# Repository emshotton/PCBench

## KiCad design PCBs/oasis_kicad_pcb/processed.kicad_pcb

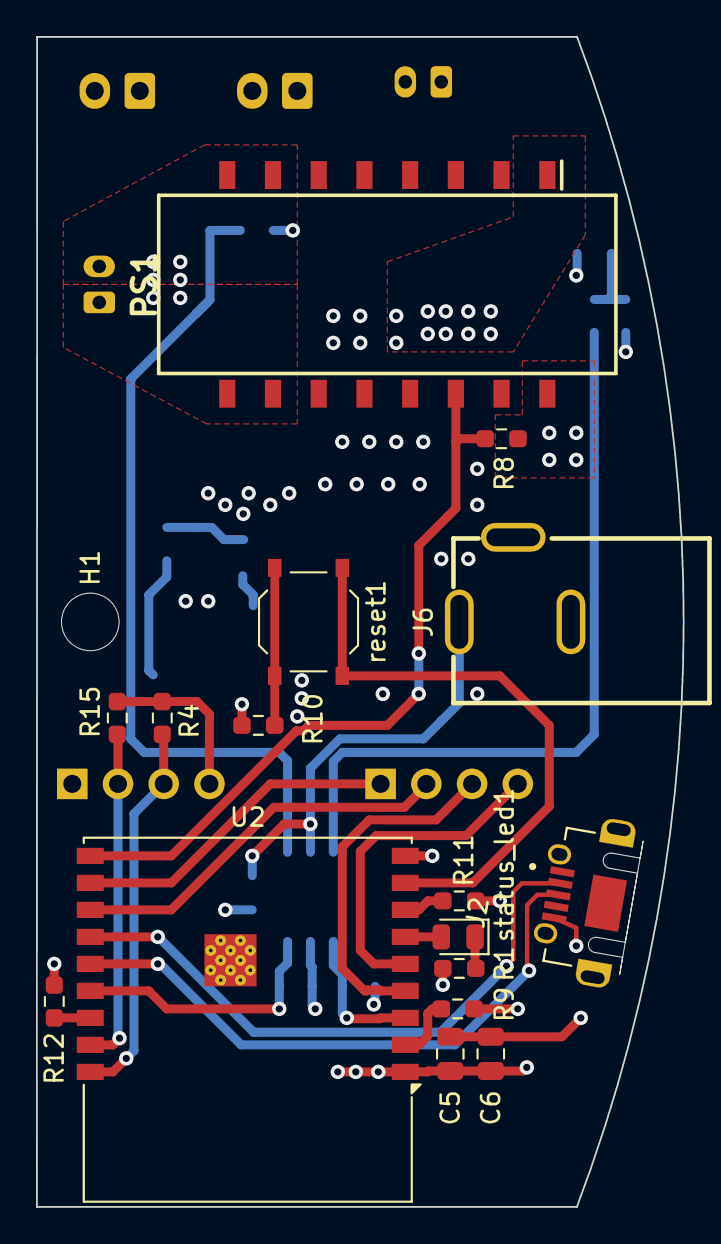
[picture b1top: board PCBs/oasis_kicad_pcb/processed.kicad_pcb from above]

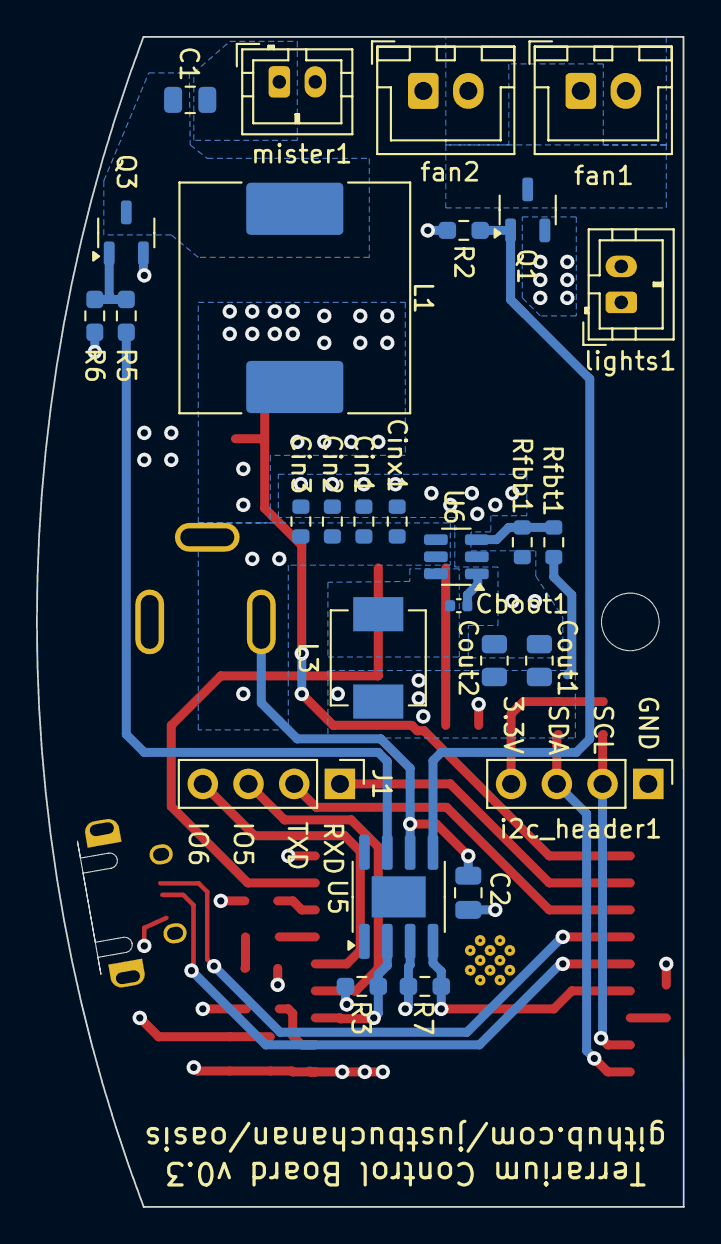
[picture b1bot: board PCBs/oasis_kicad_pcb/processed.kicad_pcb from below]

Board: 4 copper layers, 35.9 x 65.0 mm, 45 parts (28 on the bottom side), 32 nets.

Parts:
C1, C2, C6: .1uF; C_0805_2012Metric
C5: 10uF; C_0805_2012Metric
Cboot1: 100nF; C_0402_1005Metric
Cin1, Cin2, Cin3: 1uF; R_0603_1608Metric
Cinx1: 100nF; R_0603_1608Metric
Cout1, Cout2: 10uF; R_0805_2012Metric
H1: MountingHole; MountingHole_3.2mm_M3
J1: Conn_01x04; PinHeader_1x04_P2.54mm_Vertical
J2: USB_B_Micro; MOLEX_47590-0001
J6: Barrel_Jack_MountingPin; DC-IN-TH_XDJK-0051-025_JLC_C7498153
L1: 330uH; L_SXN_SMDRI127
L3: 10uH; L_Vishay_IHLP-2020
PS1: LDD-700LS; LDD-700LS-SOP254P1280X930-16N
Q1, Q3: Q_NMOS_GDS; SOT-23-3-pinswapped-mosfet
R1: 470; R_0603_1608Metric_Pad0.98x0.95mm_HandSolder
R2, R3, R5, R7, R8, R9, R10, R11, R12: 10k; R_0603_1608Metric_Pad0.98x0.95mm_HandSolder
R4, R15: 4.7k; R_0603_1608Metric_Pad0.98x0.95mm_HandSolder
R6: 10; R_0603_1608Metric_Pad0.98x0.95mm_HandSolder
Rfbb1: 22.1k; R_0603_1608Metric
Rfbt1: 69.8k; R_0603_1608Metric
U2: ESP32-C3-WROOM-02
U5: IX4427N; SOIC-8-1EP_3.9x4.9mm_P1.27mm_EP2.29x3mm
U6: LMR54406DBVR; SOT-23-6
fan1, fan2: Conn_01x02; JST_XH_B2B-XH-A_1x02_P2.50mm_Vertical
i2c_header1: Conn_01x04; PinHeader_1x04_P2.54mm_Vertical
lights1: Conn_01x02; JST_PH_B2B-PH-K_1x02_P2.00mm_Vertical
mister1: Conn_01x02; JST_PH_B2B-PH-K_1x02_P2.00mm_Vertical
reset1: SW_Push; SW_Push_1P1T_XKB_TS-1187A
status_led1: LED; LED_0805_2012Metric

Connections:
+3.3V: C5.1, C6.1, Cout1.1, Cout2.1, L3.2, R4.1, R9.1, R11.1, R12.2, R15.1, Rfbt1.1, U2.1 (3V3), i2c_header1.4
+18V: C2.1, Cin1.1, Cin2.1, Cin3.1, Cinx1.1, J6.1, L1.2, PS1.1 (+VIN), U5.6 (VCC), U6.4 (EN), U6.5 (VIN), fan1.1, fan2.1
/RXD: J1.1, U2.11 (IO20/RXD)
/TXD: J1.2, U2.12 (IO21/TXD)
/fan1_ctl: R3.1, U2.3 (IO4), U5.2 (INA)
/i2c_scl: R15.2, U2.17 (IO1), i2c_header1.2
/i2c_sda: R4.2, U2.18 (IO0), i2c_header1.3
/led_N: PS1.9 (-VOUT_1), PS1.10 (-VOUT_2), lights1.1
/led_P: PS1.7 (+VOUT_1), PS1.8 (+VOUT_2), lights1.2
/led_ctl: PS1.14 (PWM_DIM), R8.1, U2.10 (IO10)
/mist_ctl: R7.1, U2.15 (IO3), U5.4 (INB)
/usb_dminus: J2.2 (D-), U2.13 (IO18)
/usb_dplus: J2.3 (D+), U2.14 (IO19)
GND: C2.2, C5.2, C6.2, Cin1.2, Cin2.2, Cin3.2, Cinx1.2, Cout1.2, Cout2.2, J2.5 (GND), J6.2, PS1.16 (-VIN), Q1.3 (S), Q3.3 (S), R1.1, R2.2, R3.2, R5.2, R7.2, R8.2, R10.1, Rfbb1.2, U2.9 (GND), U2.19 (GND), U5.3 (GND), U6.2 (GND), i2c_header1.1, mister1.2
unnamed: J1.3, U2.4 (IO5)
unnamed: J1.4, U2.5 (IO6)
unnamed: Q1.2 (D), fan1.2, fan2.2
unnamed: Q1.1 (G), R2.1, U5.5 (OUTB)
unnamed: C1.1, L1.1, Q3.2 (D)
unnamed: Q3.1 (G), R5.1, R6.2
unnamed: R10.2, reset1.2
unnamed: R9.2, U2.2 (EN)
unnamed: R12.1, U2.16 (IO2)
unnamed: U2.6 (IO7), status_led1.2 (A)
unnamed: R11.2, U2.7 (IO8)
unnamed: U2.8 (IO9), reset1.1
unnamed: R6.1, U5.7 (OUTA)
unnamed: Cboot1.2, U6.1 (CB)
unnamed: Rfbb1.1, Rfbt1.2, U6.3 (FB)
unnamed: Cboot1.1, L3.1, U6.6 (SW)
unnamed: C1.2, mister1.1
unnamed: R1.2, status_led1.1 (K)

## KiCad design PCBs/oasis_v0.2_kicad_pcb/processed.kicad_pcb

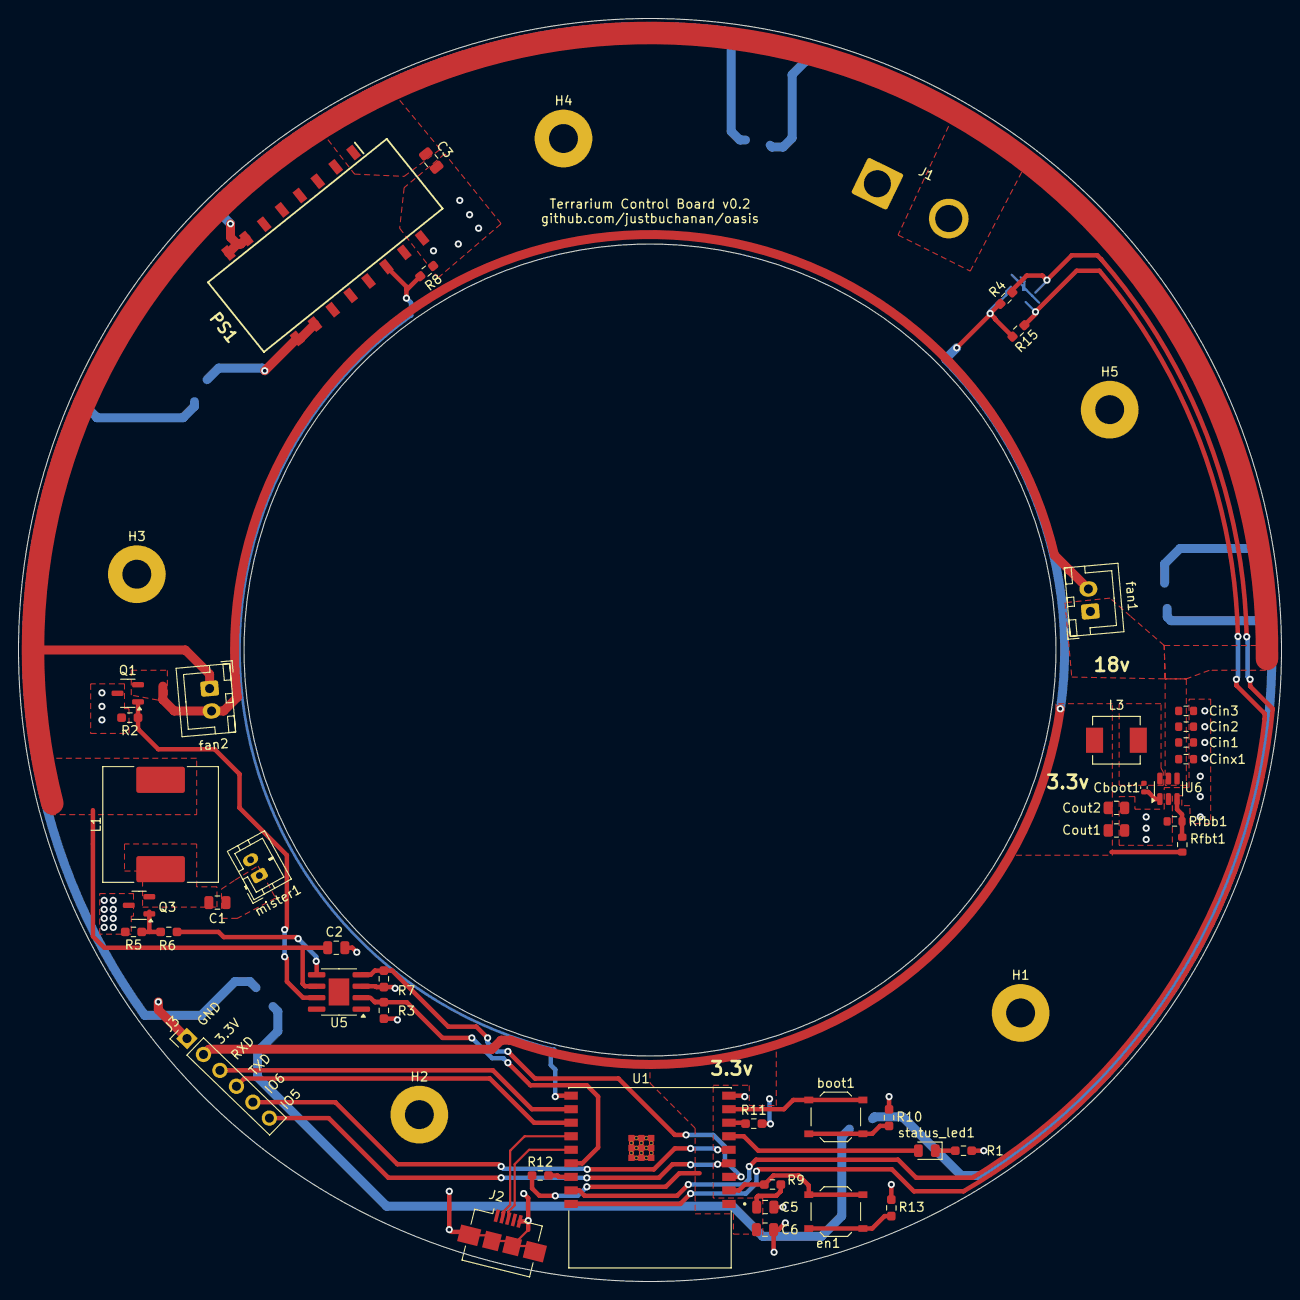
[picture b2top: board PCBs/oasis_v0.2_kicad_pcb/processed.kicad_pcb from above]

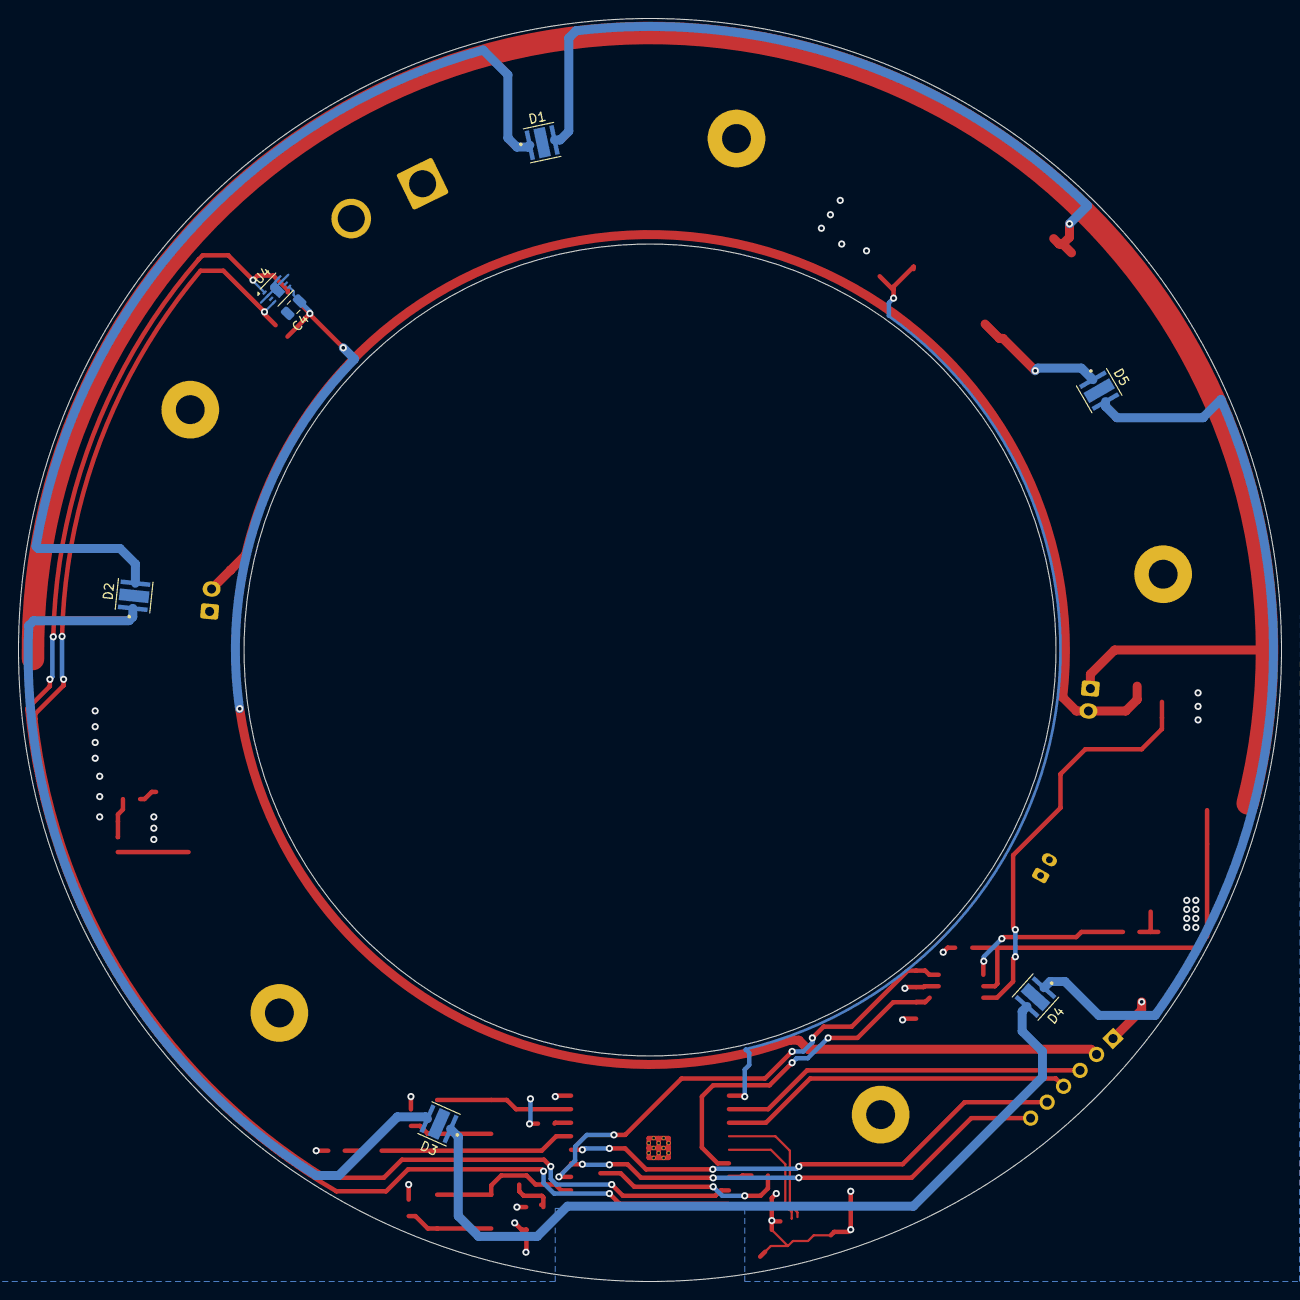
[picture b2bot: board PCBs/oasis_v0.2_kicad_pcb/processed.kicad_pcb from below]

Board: 2 copper layers, 140.0 x 140.0 mm, 57 parts (7 on the bottom side), 37 nets.

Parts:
C1, C2, C3, C4, C6: .1uF; C_0805_2012Metric
C5: 10uF; C_0805_2012Metric
Cboot1: 100nF; C_0402_1005Metric
Cin1, Cin2, Cin3: 1uF; R_0603_1608Metric
Cinx1: 100nF; R_0603_1608Metric
Cout1, Cout2: 10uF; R_0805_2012Metric
D1, D2, D3, D4, D5: LED_Pad; LED_XTEAWT-00-0000-000000F51
H1, H2, H3, H4, H5: MountingHole_Pad; MountingHole_3.2mm_M3_Pad
J1: Conn_01x02; SolderWire-2.5sqmm_1x02_P8.8mm_D2.4mm_OD4.4mm
J2: USB_B_Micro; USB_Micro-B_Amphenol_10104110_Horizontal
J3: Conn_01x06; PinHeader_1x06_P2.54mm_Vertical
L1: 330uH; L_SXN_SMDRI127
L3: 10uH; L_Vishay_IHLP-2020
PS1: LDD-700LS; LDD-700LS-SOP254P1280X930-16N
Q1, Q3: Q_NMOS_GDS; SOT-23-3
R1: 470; R_0603_1608Metric_Pad0.98x0.95mm_HandSolder
R2, R3, R5, R7, R8, R9, R10, R11, R12: 10k; R_0603_1608Metric_Pad0.98x0.95mm_HandSolder
R4, R15: 4.7k; R_0603_1608Metric_Pad0.98x0.95mm_HandSolder
R6: 10; R_0603_1608Metric_Pad0.98x0.95mm_HandSolder
R13: 1k; R_0603_1608Metric_Pad0.98x0.95mm_HandSolder
Rfbb1: 22.1k; R_0603_1608Metric
Rfbt1: 69.8k; R_0603_1608Metric
U1: ESP32-C3-WROOM-02-N4; MODULE_ESP32-C3-WROOM-02-H4
U4: SHT30-DIS; Sensirion_DFN-8-1EP_2.5x2.5mm_P0.5mm_EP1.1x1.7mm
U5: IX4427N; SOIC-8-1EP_3.9x4.9mm_P1.27mm_EP2.29x3mm
U6: LMR54406DBVR; SOT-23-6
boot1: SW_Push; SW_Push_1P1T_XKB_TS-1187A
en1: SW_Push; SW_Push_1P1T_XKB_TS-1187A
fan1, fan2: Conn_01x02; JST_XH_B2B-XH-A_1x02_P2.50mm_Vertical
mister1: Conn_01x02; JST_PH_B2B-PH-K_1x02_P2.00mm_Vertical
status_led1: LED; LED_0805_2012Metric

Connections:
+3.3V: C4.2, C5.1, C6.1, Cout1.1, Cout2.1, J3.2, L3.2, R4.1, R9.1, R11.1, R12.2, R15.1, Rfbt1.1, U1.1 (3V3), U4.5 (VDD)
+18V: C2.1, C3.2, Cin1.1, Cin2.1, Cin3.1, Cinx1.1, J1.2, L1.2, PS1.1 (+VIN), U5.6 (VCC), U6.4 (EN), U6.5 (VIN), fan1.1, fan2.1
/fan1_ctl: R3.1, U1.15 (IO3), U5.2 (INA)
/led_ctl: PS1.14 (PWM_DIM), R8.1, U1.10 (IO10)
/mist_ctl: R7.1, U1.3 (IO4), U5.4 (INB)
/usb_dminus: J2.2 (D-), U1.13 (IO18)
/usb_dplus: J2.3 (D+), U1.14 (IO19)
GND: C2.2, C3.1, C4.1, C5.2, C6.2, Cin1.2, Cin2.2, Cin3.2, Cinx1.2, Cout1.2, Cout2.2, D1.3 (PAD), D2.3 (PAD), D3.3 (PAD), D4.3 (PAD), D5.3 (PAD), J1.1, J2.5 (GND), J2.6 (Shield), J3.1, PS1.16 (-VIN), Q1.3 (S), Q3.3 (S), R1.1, R2.2, R3.2, R5.2, R7.2, R8.2, R10.1, R13.1, Rfbb1.2, U1.9 (GND), U1.19 (GND), U1.20 (GND), U1.21 (GND), U1.22 (GND), U1.23 (GND), U1.24 (GND), U1.25 (GND), U1.26 (GND), U1.27 (GND), U1.28 (GND), U1.29 (GND), U1.30 (GND), U1.31 (GND), U1.32 (GND), U1.33 (GND), U1.34 (GND), U1.35 (GND), U1.36 (GND), U1.37 (GND), U1.38 (GND), U1.39 (GND), U4.2 (ADDR), U4.7 (R), U4.8 (VSS), U4.9 (VSS), U5.3 (GND), U6.2 (GND), mister1.2
unnamed: D1.2 (A), PS1.7 (+VOUT_1), PS1.8 (+VOUT_2)
unnamed: D1.1 (K), D2.2 (A)
unnamed: D2.1 (K), D3.2 (A)
unnamed: D3.1 (K), D4.2 (A)
unnamed: D4.1 (K), D5.2 (A)
unnamed: D5.1 (K), PS1.9 (-VOUT_1), PS1.10 (-VOUT_2)
unnamed: J3.3, U1.11 (RXD)
unnamed: J3.4, U1.12 (TXD)
unnamed: J3.5, U1.5 (IO6)
unnamed: J3.6, U1.4 (IO5)
unnamed: Q1.2 (D), fan1.2, fan2.2
unnamed: Q1.1 (G), R2.1, U5.7 (OUTA)
unnamed: C1.1, L1.1, Q3.2 (D)
unnamed: Q3.1 (G), R5.1, R6.2
unnamed: R10.2, boot1.2
unnamed: R13.2, en1.1
unnamed: R9.2, U1.2 (EN), en1.2
unnamed: R4.2, U1.18 (IO0), U4.1 (SDA)
unnamed: R15.2, U1.17 (IO1), U4.4 (SCL)
unnamed: R12.1, U1.16 (IO2)
unnamed: U1.6 (IO7), status_led1.2 (A)
unnamed: R11.2, U1.7 (IO8)
unnamed: U1.8 (IO9), boot1.1
unnamed: R6.1, U5.5 (OUTB)
unnamed: Cboot1.2, U6.1 (CB)
unnamed: Rfbb1.1, Rfbt1.2, U6.3 (FB)
unnamed: Cboot1.1, L3.1, U6.6 (SW)
unnamed: C1.2, mister1.1
unnamed: R1.2, status_led1.1 (K)

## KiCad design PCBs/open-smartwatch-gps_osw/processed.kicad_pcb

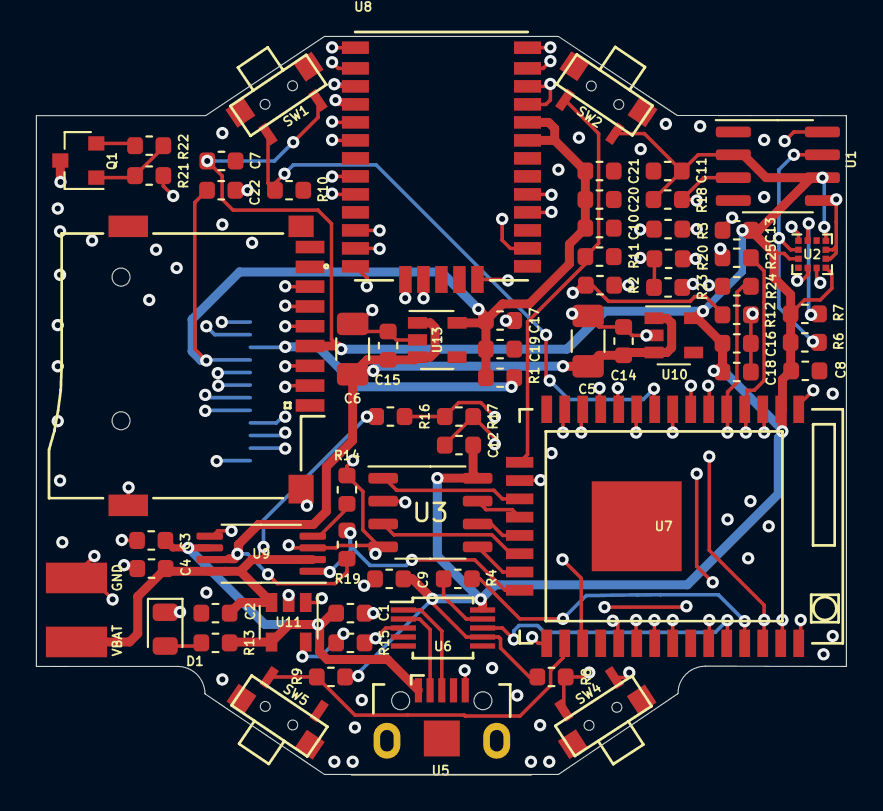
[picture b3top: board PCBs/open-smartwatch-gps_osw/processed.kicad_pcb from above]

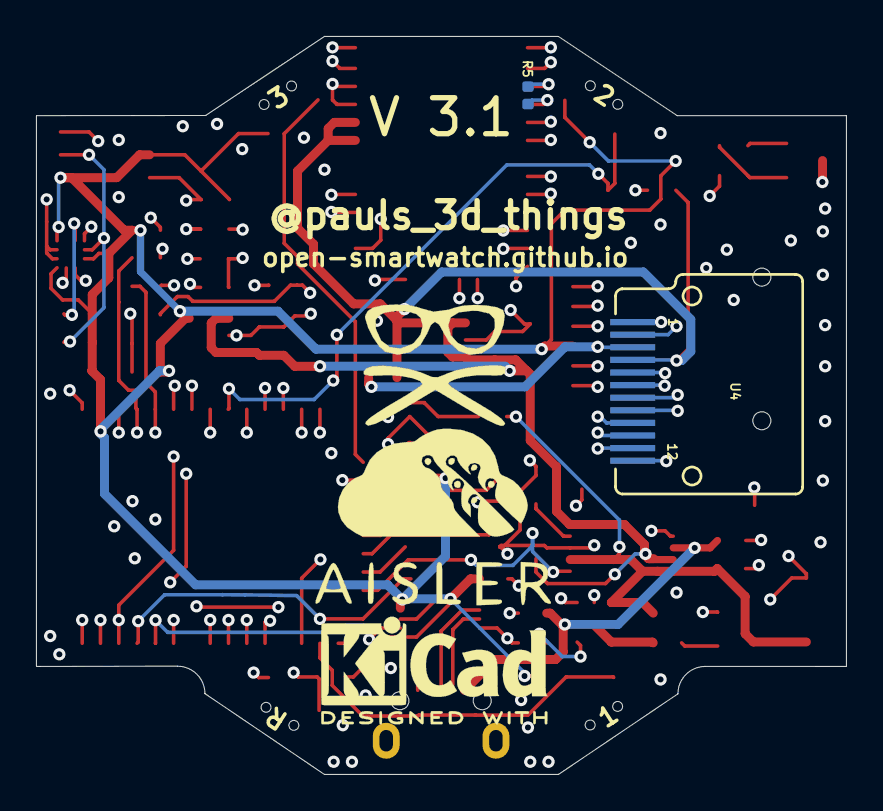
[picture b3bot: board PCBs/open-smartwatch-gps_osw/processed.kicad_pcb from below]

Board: 4 copper layers, 45.0 x 41.0 mm, 67 parts (2 on the bottom side), 55 nets.

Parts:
C1, C2: 4.7uF; C_0603_1608Metric
C3, C4, C7, C8, C9, C10, C11, C12, C13, C14, C15, C18, C19, C22: 0.1u; C_0603_1608Metric
C5, C6: 100u; C_1206_3216Metric
C16, C17: 4.7u; C_0603_1608Metric
C20: 100p; C_0603_1608Metric
C21: 10p; C_0603_1608Metric
D1: LED_Green; LED_0805_2012Metric
J1: Conn_01x02; PinHeader_1x02_P2.54mm_Vertical
Q1: 2N7002; SOT-23
R1: 22; R_0603_1608Metric
R2, R3, R6, R7, R24, R25: 1k; R_0603_1608Metric
R4, R13: 470R; R_0603_1608Metric
R5: 0R; R_0402_1005Metric
R8, R9, R10, R11, R17, R20, R21: 10k; R_0603_1608Metric
R12: 5.6k; R_0603_1608Metric
R14: 510R; R_0603_1608Metric
R15: 5k; R_0603_1608Metric
R16, R19: 200k; R_0603_1608Metric
R18: 2.2K; R_0603_1608Metric
R22: 1M; R_0603_1608Metric
R23: 56k; R_0603_1608Metric
SW1, SW2, SW4, SW5: SW_Push; button_side_smd
U1: DS3231MZ; SOIC-8_3.9x4.9mm_P1.27mm
U2: BMA400; LGA-12_2x2mm_P0.5mm
U3: PSRAM64H; SOP-8_3.9x4.9mm_P1.27mm
U4: GC9A01_IPS_display
U5: USB-OTG; USBmicro-B
U6: CH340E; MSOP-10_3x3mm_P0.5mm
U7: ttgo-32-micro
U8: Quectel_L96
U9: TPS2115A; TSSOP-8_4.4x3mm_P0.65mm
U10, U13: XC6209; SOT-23-5
U11: MCP73831T-2ACI_OT; SOT-23-5
XS1: SD_ebay-uSD-push_push_SMD; Conn_uSDcard

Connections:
+3V3: C7.1, C8.1, C9.1, C11.1, C12.1, C13.1, C16.1, C18.1, R6.1, R7.1, R8.1, R9.1, R18.2, SW1.2, SW2.2, U1.2, U1.6, U2.3, U2.7, U2.10, U3.8, U6.7, U6.10, U7.2, U10.5, XS1.4
/3DFIX_2V8: R25.1, U8.2
/3DFIX_3V3: R25.2, U7.4
/3V3_2: C10.1, C17.1, C19.1, C20.1, C21.1, C22.1, R1.1, U4.4, U8.8, U8.9, U13.5
/ANT: R5.2, U8.17
/BTN2: R10.1, SW1.1, U7.9
/BTN3: R11.1, SW2.1, U7.16
/B_MON: R16.2, R17.1, U7.10
/CLK: U3.6, U7.20
/D_N: U5.4, U6.2
/D_P: U5.3, U6.1
/EN: R8.2, SW4.2, U7.3
/FLASH: R9.2, SW5.2, U7.25
/GEO_F2V8: R24.1, U8.24
/GEO_F3V3: R24.2, U7.5
/GPIO10: U3.1, U7.18
/GPS_FON2V8: R20.1, R23.2, U8.28
/GPS_FON3V3: R20.2, U7.11
/GPS_RX2V8: R2.1, R12.2, U8.26
/GPS_RX3V3: R2.2, U7.13
/GPS_TX2V8: R3.1, U8.25
/GPS_TX3V3: R3.2, U7.12
/IO34: U2.5, U7.6
/IO35: U2.6, U7.7
/LEDK: Q1.3, U4.2
/MISO: U7.31, XS1.7
/MOSI: U4.10, U7.37, XS1.3
/PIN_LED: R21.2, U7.17
/RTC_INT: R18.1, U1.3, U7.8
/RX: U6.8, U7.34
/SCK: U4.9, U7.30, XS1.5
/SCL: R7.2, U1.8, U2.12, U7.36
/SD0: U3.2, U7.28
/SD1: U3.5, U7.22
/SD2: U3.7, U7.19
/SD3: U3.3, U7.21
/SDA: R6.2, U1.7, U2.2, U7.33
/SD_CS: U7.26, XS1.2
/STAT_PWR: R19.2, U7.23, U9.1
/TFT_CS: U4.8, U7.29
/TFT_DC: U4.7, U7.14
/TFT_RST: U4.11, U7.24
/TX: R4.2, U7.35
/VBAT: C2.1, C4.1, J1.1, R16.1, U9.2, U9.8, U11.3
/VBUS: C1.2, C3.1, R13.2, U5.5, U9.6, U11.4
/VCC: C5.1, C6.1, C14.1, C15.1, R19.1, U9.7, U10.1, U10.3, U13.1, U13.3
GND: C1.1, C2.2, C3.2, C4.2, C5.2, C6.2, C7.2, C8.2, C9.2, C10.2, C11.2, C12.2, C13.2, C14.2, C15.2, C16.2, C17.2, C18.2, C19.2, C20.2, C21.2, C22.2, J1.2, Q1.2, R10.2, R11.2, R12.1, R14.2, R15.2, R17.2, R22.1, R23.1, SW4.1, SW5.1, U1.5, U2.1, U2.8, U2.9, U3.4, U4.1, U4.5, U4.6, U4.12, U5.1, U6.3, U7.1, U7.15, U7.38, U8.4, U8.5, U8.10, U8.11, U8.12, U8.13, U8.14, U8.15, U8.18, U8.19, U8.21, U8.22, U8.27, U8.31, U9.3, U9.5, U10.2, U11.2, U13.2, XS1.6
unnamed: D1.1, U11.1
unnamed: D1.2, R13.1
unnamed: Q1.1, R21.1, R22.2
unnamed: R1.2, U4.3
unnamed: R4.1, U6.9
unnamed: R5.1, U8.16
unnamed: R14.1, U9.4
unnamed: R15.1, U11.5

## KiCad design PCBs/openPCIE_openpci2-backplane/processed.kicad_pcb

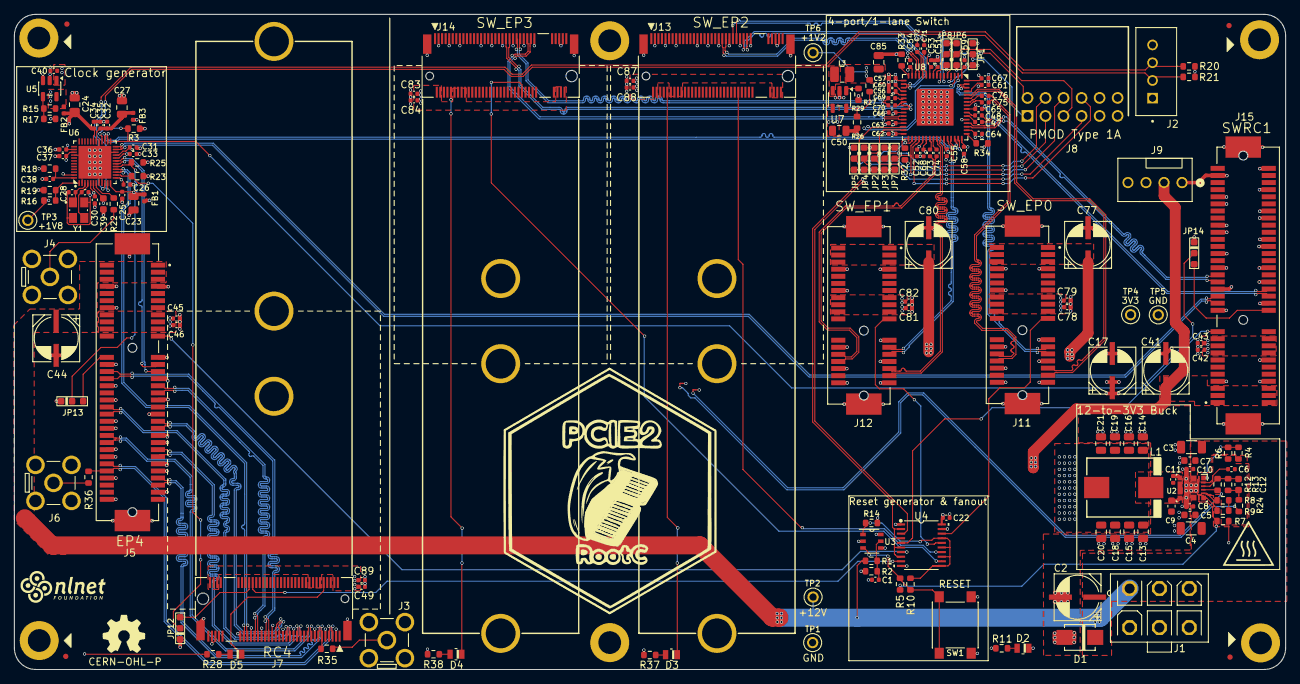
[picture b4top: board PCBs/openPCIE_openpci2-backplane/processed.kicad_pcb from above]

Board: 4 copper layers, 179.1 x 92.3 mm, 190 parts (0 on the bottom side), 133 nets.

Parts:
C1, C38, C42, C45, C49, C78, C81, C83, C87: 10n; C_0402_1005Metric
C2, C17, C41, C44, C77, C80: 100u; CAPAE660X610N
C3, C4: 10u; C_1206_3216Metric
C5, C7, C9, C39: 1u; C_0603_1608Metric
C6, C8, C10, C11, C22, C25, C26, C30, C31, C32, C33, C34, C35, C36, C37, C40, C43, C46, C47, C48, C51, C52, C53, C54, C55, C56, C57, C58, C59, C60, C61, C62, C63, C64, C65, C66, C67, C68, C69, C70, C71, C72, C73, C74, C75, C76, C79, C82, C84, C88, C89: 100n; C_0402_1005Metric
C12: N.C.; C_0603_1608Metric
C13, C14, C15, C16, C18, C19, C20, C21, C23, C24, C27, C50, C85: 22u; C_0805_2012Metric
C28, C29: 8p; C_0402_1005Metric
D1: SMBJ12A; DIOM4336X265N
D2: LTST-C170KRKT; LED_LTST-C170KGKT_LTO-L
D3, D4, D5: LTST-C170KGKT; LED_LTST-C170KGKT_LTO-L
FB1, FB2, FB3: 220R; L_0402_1005Metric
FM1, FM2, FM3, FM4: Fiducial_0.75mm_Mask1.5mm
H1, H2, H3, H4, H5, H6: Nylon Standoff M3x11; Mounting_hole 3.2_5.5mm_NO_NET
J1: DLL-5566-6A; MINIFIT_5566-06A
J2: B4B-XH-A
J3, J4, J6: BWSMA-KWE-Z001
J5, J15: X3113WVS-64-9TV01; 10061913-111PLF
J7, J13, J14: AS0BC21-S30BM-7H; 1-2199230-6 with holes (80 mm)
J8: 10129382-912001BLF; SSQ-106-02-T-D-RA
J9: M2510V-04P-N3
J11, J12: X1618WVS-36-9TV30; 10061913-110PLF
JP1, JP2, JP3, JP4, JP5: 10K; JP3 shorted with 0R (0603)
JP6, JP7, JP8: 2K2; JP3 shorted with 0R (0603) 2-3
JP12, JP13, JP14: 0K; JP3 shorted with 0R (0603) 2-3
L1: 7443082015A; WE-HCM_1088A
L3: 2u2; L_1008_2520Metric
LOGO1: Open hardware logo; Open HW logo
LOGO2: NLnet logo
LOGO3: PCIE2 logo
NT1, NT2, NT3: NetTie_2; NetTie-2_SMD_Pad0.2mm
R1: 255K; R_0603_1608Metric
R2, R3, R7, R12, R14, R16, R18, R19, R23, R25, R26, R27, R29: 10K; R_0603_1608Metric
R4, R13: 56K; R_0603_1608Metric
R5, R10: 0R; R_0603_1608Metric
R6, R33, R34: 12K1; R_0603_1608Metric
R8: 4K32; R_0603_1608Metric
R9: 182K; R_0603_1608Metric
R11, R28, R37, R38: 220R; R_0603_1608Metric
R15: 75K; R_0603_1608Metric
R17: 33K; R_0603_1608Metric
R20, R21, R32: 2K2; R_0603_1608Metric
R22, R24, R35, R36: 33R; R_0603_1608Metric
SW1: PTS645SK50SMTR92 LFS; PTS645
TP1, TP2, TP3, TP4, TP5, TP6: Test; 5000
U2: TPS54KC23RZRR; RZR0016A-MFG
U3: NCV308SNADJT1G; TSOP-6_318G-02_ONS-L
U4: SN74LVC244APWR; PW20-L
U5: TLV75801PDBVR; SOT-23-5
U6: PI6CG18801ZLIEX; QFN40P600X600X90-49N
U7: RY3420
U8: ASM1184E; QFN-64-1EP_9x9mm_P0.5mm_EP5.2x5.2mm
Y1: TSX-3225 25.0000MF20X-AJ0; XTAL_TSX-3225_25.0000MF20X-AJ3

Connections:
+3V3: C13.1, C14.2, C15.1, C16.2, C17.+, C18.1, C19.2, C20.1, C21.2, C22.2, C40.1, C42.2, C43.2, C45.2, C46.2, C49.2, C50.1, C53.2, C56.2, C59.2, C62.2, C65.2, C68.2, C78.2, C79.2, C81.2, C82.2, C83.2, C84.2, C87.2, C88.2, C89.2, J2.4, J5.A9 (+3.3V), J5.A10 (+3.3V), J5.B8 (+3.3V), J5.B10 (3.3Vaux), J7.2 (3.3V), J7.4 (3.3V), J7.12 (3.3V), J7.14 (3.3V), J7.16 (3.3V), J7.18 (3.3V), J7.70 (3.3V), J7.72 (3.3V), J7.74 (3.3V), J8.6 (VCC), J8.12 (VCC), J11.A9 (+3.3V), J11.A10 (+3.3V), J11.B8 (+3.3V), J11.B10 (3.3Vaux), J12.A9 (+3.3V), J12.A10 (+3.3V), J12.B8 (+3.3V), J12.B10 (3.3Vaux), J13.2 (3.3V), J13.4 (3.3V), J13.12 (3.3V), J13.14 (3.3V), J13.16 (3.3V), J13.18 (3.3V), J13.70 (3.3V), J13.72 (3.3V), J13.74 (3.3V), J14.2 (3.3V), J14.4 (3.3V), J14.12 (3.3V), J14.14 (3.3V), J14.16 (3.3V), J14.18 (3.3V), J14.70 (3.3V), J14.72 (3.3V), J14.74 (3.3V), J15.A9 (+3.3V), J15.A10 (+3.3V), J15.B8 (+3.3V), J15.B10 (3.3Vaux), JP1.1, JP2.1, JP3.1, JP4.1, JP5.1, JP6.1, JP7.1, JP8.1, L1.2, NT3.2, R7.2, R11.1, R14.1, R20.2, R21.2, R28.1, R29.1, R37.1, R38.1, TP4.1, U3.4 (CT), U3.6 (VDD), U4.20 (VCC), U5.1 (IN), U5.3 (EN), U7.4 (IN), U8.1 (3V_AUX), U8.10 (3V3), U8.21 (3V3), U8.32 (3V3), U8.38 (3V3), U8.56 (3V3)
+12V: C2.+, C3.2, C4.2, C5.2, C7.2, C8.2, C10.2, C41.+, C44.+, C77.+, C80.+, D1.C, J1.1, J1.2, J1.3, J5.A2 (+12V), J5.A3 (+12V), J5.B1 (+12V), J5.B2 (+12V), J5.B3 (+12V), J9.2, J11.A2 (+12V), J11.A3 (+12V), J11.B1 (+12V), J11.B2 (+12V), J11.B3 (+12V), J12.A2 (+12V), J12.A3 (+12V), J12.B1 (+12V), J12.B2 (+12V), J12.B3 (+12V), J15.A2 (+12V), J15.A3 (+12V), J15.B1 (+12V), J15.B2 (+12V), J15.B3 (+12V), R1.1, R4.2, TP2.1, U2.3 (VIN), U2.9 (VIN)
/Clock generator & Reset fanout/LDO_1V8: C39.2, FB1.1, FB2.1, FB3.1, R3.2, R15.2, R16.2, R18.2, R23.1, R25.1, TP3.1, U5.5 (OUT), U6.6 (VDD_REFOUT)
/Clock generator & Reset fanout/PGOOD: R5.2, R7.1, U2.10 (PG)
/Clock generator & Reset fanout/REFOUT: J4.1 (In), R22.2
/Clock generator & Reset fanout/VDDA: C27.1, C32.2, C35.2, FB3.2, U6.30 (VDDA)
/Clock generator & Reset fanout/VDDO: C24.1, C26.2, C31.2, C34.2, C37.2, FB2.2, U6.13 (VDDO), U6.21 (VDDO), U6.31 (VDDO), U6.39 (VDDO), U6.47 (VDDO)
/Clock generator & Reset fanout/VDD_DIG: C23.1, C25.2, C30.2, C33.2, C36.2, FB1.2, U6.5 (VDD_OSC), U6.12 (VDD_DIG), U6.20 (VDD), U6.38 (VDD)
/PCIe switch/GPIO0: J8.1 (IO1), JP1.2, U8.4 (GPIO_0)
/PCIe switch/GPIO1: J8.2 (IO2), JP4.2, U8.31 (GPIO_1)
/PCIe switch/GPIO2: J8.3 (IO3), JP6.2, U8.5 (GPIO_2)
/PCIe switch/GPIO3: J8.4 (IO4), JP2.2, U8.34 (GPIO_3)
/PCIe switch/GPIO4: J8.7 (IO5), JP8.2, U8.8 (GPIO_4)
/PCIe switch/GPIO5: J8.8 (IO6), JP5.2, U8.30 (GPIO_5)
/PCIe switch/GPIO6: J8.9 (IO7), JP7.2, U8.35 (GPIO_6)
/PCIe switch/GPIO7: J8.10 (IO8), JP3.2, U8.36 (GPIO_7)
/PCIe switch/S0TX_N: C76.1, U8.58 (TXN_4)
/PCIe switch/S0TX_P: C75.1, U8.57 (TXP_4)
/PCIe switch/S1TX_N: C74.1, U8.40 (TXN_3)
/PCIe switch/S1TX_P: C73.1, U8.39 (TXP_3)
/PCIe switch/S2TX_N: C72.1, U8.12 (TXN_1)
/PCIe switch/S2TX_P: C71.1, U8.11 (TXP_1)
/PCIe switch/S3TX_N: C70.1, U8.23 (TXN_2)
/PCIe switch/S3TX_P: C69.1, U8.22 (TXP_2)
/PCIe switch/STX_IN_N: C48.1, U8.55 (TXN_IN)
/PCIe switch/STX_IN_P: C47.1, U8.54 (TXP_IN)
EP4_CLK_N: J5.A14 (REFclk-), U6.19 (Q1-)
EP4_CLK_P: J5.A13 (REFclk+), U6.18 (Q1+)
GND: C1.1, C2.-, C3.1, C4.1, C5.1, C7.1, C8.1, C9.1, C10.1, C13.2, C14.1, C15.2, C16.1, C17.-, C18.2, C19.1, C20.2, C21.1, C22.1, C23.2, C24.2, C25.1, C26.1, C27.2, C28.2, C29.1, C30.1, C31.1, C32.1, C33.1, C34.1, C35.1, C36.1, C37.1, C38.1, C39.1, C40.2, C41.-, C42.1, C43.1, C44.-, C45.1, C46.1, C49.1, C50.2, C51.1, C52.1, C53.1, C54.1, C55.1, C56.1, C57.1, C58.1, C59.1, C60.1, C61.1, C62.1, C63.1, C64.1, C65.1, C66.1, C67.1, C68.1, C77.-, C78.1, C79.1, C80.-, C81.1, C82.1, C83.1, C84.1, C85.2, C87.1, C88.1, C89.1, D1.A, D2.C, J1.4, J1.5, J1.6, J2.1, J3.2 (Ext), J4.2 (Ext), J5.A4 (GND), J5.A12 (GND), J5.A15 (GND), J5.A18 (GND), J5.A20 (GND), J5.A23 (GND), J5.A24 (GND), J5.A27 (GND), J5.A28 (GND), J5.A31 (GND), J5.B4 (GND), J5.B7 (GND), J5.B13 (GND), J5.B16 (GND), J5.B18 (GND), J5.B21 (GND), J5.B22 (GND), J5.B25 (GND), J5.B26 (GND), J5.B29 (GND), J5.B32 (GND), J5.SH, J6.2 (Ext), J7.3 (GND), J7.9 (GND), J7.15 (GND), J7.27 (GND), J7.33 (GND), J7.39 (GND), J7.45 (GND), J7.51 (GND), J7.57 (GND), J7.71 (GND), J7.73 (GND), J7.76 (GND), J7.77 (GND), J7.GND1 (Gnd), J7.GND2 (Gnd), J7.GND3 (Gnd), J8.5 (GND), J8.11 (GND), J9.1, J11.A4 (GND), J11.A12 (GND), J11.A15 (GND), J11.A18 (GND), J11.B4 (GND), J11.B7 (GND), J11.B13 (GND), J11.B16 (GND), J11.B18 (GND), J11.SH, J12.A4 (GND), J12.A12 (GND), J12.A15 (GND), J12.A18 (GND), J12.B4 (GND), J12.B7 (GND), J12.B13 (GND), J12.B16 (GND), J12.B18 (GND), J12.SH, J13.3 (GND), J13.9 (GND), J13.15 (GND), J13.27 (GND), J13.33 (GND), J13.39 (GND), J13.45 (GND), J13.51 (GND), J13.57 (GND), J13.71 (GND), J13.73 (GND), J13.76 (GND), J13.77 (GND), J13.GND1 (Gnd), J13.GND2 (Gnd), J13.GND3 (Gnd), J14.3 (GND), J14.9 (GND), J14.15 (GND), J14.27 (GND), J14.33 (GND), J14.39 (GND), J14.45 (GND), J14.51 (GND), J14.57 (GND), J14.71 (GND), J14.73 (GND), J14.76 (GND), J14.77 (GND), J14.GND1 (Gnd), J14.GND2 (Gnd), J14.GND3 (Gnd), J15.A4 (GND), J15.A12 (GND), J15.A15 (GND), J15.A18 (GND), J15.A20 (GND), J15.A23 (GND), J15.A24 (GND), J15.A27 (GND), J15.A28 (GND), J15.A31 (GND), J15.B4 (GND), J15.B7 (GND), J15.B13 (GND), J15.B16 (GND), J15.B18 (GND), J15.B21 (GND), J15.B22 (GND), J15.B25 (GND), J15.B26 (GND), J15.B29 (GND), J15.B32 (GND), J15.SH, JP1.3, JP2.3, JP3.3, JP4.3, JP5.3, JP6.3, JP7.3, JP8.3, JP12.3, JP13.3, JP14.3, NT1.2, NT2.2, R2.2, R17.1, R19.2, R26.1, R32.2, R33.2, R34.2, SW1.1, TP1.1, TP5.1, U2.4 (PGND), U2.8 (PGND), U2.16 (PGND), U3.2 (GND), U4.1 (~1OE), U4.10 (GND), U4.19 (~2OE), U5.2 (GND), U6.2 (GND_XTAL), U6.8 (GND_REFOUT), U6.9 (GND_DIG), U6.22 (GND), U6.29 (GNDA), U6.40 (GND), U6.49 (EPAD), U7.2 (GND), U8.53 (GND), U8.65 (GND), Y1.2, Y1.4
unnamed: C12.2, R13.1, R24.1
unnamed: D2.A, R11.2
unnamed: D3.A, R37.2
unnamed: D4.A, R38.2
unnamed: D5.A, R28.2
unnamed: J3.1 (In), R35.2
unnamed: J6.1 (In), R36.2
unnamed: D5.C, J7.10 (DAS/~DSS/~LED1)
unnamed: D3.C, J13.10 (DAS/~DSS/~LED1)
unnamed: D4.C, J14.10 (DAS/~DSS/~LED1)
unnamed: NT3.1, R24.2
unnamed: C51.2, C52.2, C54.2, C55.2, C57.2, C58.2, C60.2, C61.2, C63.2, C64.2, C66.2, C67.2, C85.1, L3.2, R27.2, TP6.1, U8.9 (1V2), U8.15 (1V2), U8.17 (1V2), U8.20 (1V2), U8.26 (1V2), U8.29 (1V2), U8.37 (1V2), U8.43 (1V2), U8.48 (1V2), U8.50 (1V2), U8.61 (1V2), U8.64 (1V2)
unnamed: C6.1, NT1.1, R6.1, R8.1, R9.1, U2.2 (AGND)
unnamed: C11.2, U2.5 (BOOT)
unnamed: R4.1, R6.2, U2.1 (EN)
unnamed: C12.1, R12.2, R13.2, U2.14 (FB)
unnamed: NT2.1, R12.1, U2.13 (GOSNS)
unnamed: R8.2, U2.12 (ILIM)
unnamed: R9.2, U2.11 (MSEL)
unnamed: C6.2, U2.15 (SS)
unnamed: C11.1, L1.1, U2.6 (SW)
unnamed: C9.2, U2.7 (VCC)
unnamed: C1.2, R1.2, R2.1, U3.5 (SENSE)
unnamed: R5.1, R10.2, SW1.2, U3.3 (~MR)
unnamed: R10.1, R14.2, U3.1 (~RESET), U4.11 (2A1), U4.13 (2A2), U4.15 (2A3), U4.17 (2A4)
unnamed: R15.1, R17.2, U5.4 (FB)
unnamed: R22.1, U6.7 (SADR/REFOUT)
unnamed: R16.1, R19.1, U6.1 (SS_SEL_TRI)
unnamed: C28.1, U6.3 (XTAL_IN/CLK), Y1.1
unnamed: C29.2, U6.4 (XTAL_OUT), Y1.3
unnamed: JP12.2, R23.2, U6.14 (~OE0)
unnamed: JP13.2, R25.2, U6.17 (~OE1)
unnamed: JP14.2, R3.1, U6.25 (~OE2), U6.28 (~OE3)
unnamed: C38.2, R18.1, U6.48 (~PD)
unnamed: R29.2, U7.1 (EN)
unnamed: R26.2, R27.1, U7.5 (FB)
unnamed: L3.1, U7.3 (SW)
unnamed: R33.1, U8.16 (REXT1)
unnamed: R34.1, U8.49 (REXT2)
unnamed: R32.1, U8.33 (TEST_EN)
PCIESW_CLK_N: U6.27 (Q3-), U8.47 (REFCLKN_IN)
PCIESW_CLK_P: U6.26 (Q3+), U8.46 (REFCLKP_IN)
RC4_CLK_N: J7.53 (REFCLKn), U6.16 (Q0-)
RC4_CLK_P: J7.55 (REFCLKp), U6.15 (Q0+)
RC4_RX0_N: J5.B15 (PETn0), J7.41 (PERn0/SATA-B+)
RC4_RX0_P: J5.B14 (PETp0), J7.43 (PERp0/SATA-B-)
RC4_RX1_N: J5.B20 (PETn1), J7.29 (PERn1)
RC4_RX1_P: J5.B19 (PETp1), J7.31 (PERp1)
RC4_RX2_N: J5.B24 (PETn2), J7.17 (PERn2)
RC4_RX2_P: J5.B23 (PETp2), J7.19 (PERp2)
RC4_RX3_N: J5.B28 (PETn3), J7.5 (PERn3), R36.1
RC4_RX3_P: J5.B27 (PETp3), J7.7 (PERp3)
RC4_TX0_N: J5.A17 (PERn0), J7.47 (PETn0/SATA-A-)
RC4_TX0_P: J5.A16 (PERp0), J7.49 (PETp0/SATA-A+)
RC4_TX1_N: J5.A22 (PERn1), J7.35 (PETn1)
RC4_TX1_P: J5.A21 (PERp1), J7.37 (PETp1)
RC4_TX2_N: J5.A26 (PERn2), J7.23 (PETn2)
RC4_TX2_P: J5.A25 (PERp2), J7.25 (PETp2)
RC4_TX3_N: J5.A30 (PERn3), J7.11 (PETn3), R35.1
RC4_TX3_P: J5.A29 (PERp3), J7.13 (PETp3)
SCL_3V3: J2.3, R20.1, U6.10 (SCLK), U8.6 (MSCLK)
SDA_3V3: J2.2, R21.1, U6.11 (SDATA), U8.7 (MSDA)
SWRC1_CLK_N: J15.A14 (REFclk-), U6.24 (Q2-)
SWRC1_CLK_P: J15.A13 (REFclk+), U6.23 (Q2+)
SWRC1_RX_N: J15.A17 (PERn0), U8.52 (RXN_IN)
SWRC1_RX_P: J15.A16 (PERp0), U8.51 (RXP_IN)
SWRC1_TX_N: C48.2, J15.B15 (PETn0)
SWRC1_TX_P: C47.2, J15.B14 (PETp0)
SW_SLOT0_CLK_N: J11.A14 (REFCLK-), U8.63 (REFCLKN_4)
SW_SLOT0_CLK_P: J11.A13 (REFCLK+), U8.62 (REFCLKP_4)
SW_SLOT0_RX_N: J11.A17 (PERn0), U8.60 (RXN_4)
SW_SLOT0_RX_P: J11.A16 (PERp0), U8.59 (RXP_4)
SW_SLOT0_TX_N: C76.2, J11.B15 (PETn0)
SW_SLOT0_TX_P: C75.2, J11.B14 (PETp0)
SW_SLOT1_CLK_N: J12.A14 (REFCLK-), U8.45 (REFCLKN_3)
SW_SLOT1_CLK_P: J12.A13 (REFCLK+), U8.44 (REFCLKP_3)
SW_SLOT1_RX_N: J12.A17 (PERn0), U8.42 (RXN_3)
SW_SLOT1_RX_P: J12.A16 (PERp0), U8.41 (RXP_3)
SW_SLOT1_TX_N: C74.2, J12.B15 (PETn0)
SW_SLOT1_TX_P: C73.2, J12.B14 (PETp0)
SW_SLOT2_CLK_N: J13.53 (REFCLKn), U8.19 (REFCLKN_1)
SW_SLOT2_CLK_P: J13.55 (REFCLKp), U8.18 (REFCLKP_1)
SW_SLOT2_RX_N: J13.41 (PERn0/SATA-B+), U8.14 (RXN_1)
SW_SLOT2_RX_P: J13.43 (PERp0/SATA-B-), U8.13 (RXP_1)
SW_SLOT2_TX_N: C72.2, J13.47 (PETn0/SATA-A-)
SW_SLOT2_TX_P: C71.2, J13.49 (PETp0/SATA-A+)
SW_SLOT3_CLK_N: J14.53 (REFCLKn), U8.28 (REFCLKN_2)
SW_SLOT3_CLK_P: J14.55 (REFCLKp), U8.27 (REFCLKP_2)
SW_SLOT3_RX_N: J14.41 (PERn0/SATA-B+), U8.25 (RXN_2)
SW_SLOT3_RX_P: J14.43 (PERp0/SATA-B-), U8.24 (RXP_2)
SW_SLOT3_TX_N: C70.2, J14.47 (PETn0/SATA-A-)
SW_SLOT3_TX_P: C69.2, J14.49 (PETp0/SATA-A+)
~EP4_CLKREQ: J5.B12 (~CLKREQ), JP13.1
~EP4_RST: J5.A11 (~PERST), U4.7 (2Y2)
~PCIESW_IN_RST: U4.3 (2Y4), U8.3 (RES_IN)
~PCIESW_OUT_RST: U4.2 (1A1), U4.4 (1A2), U4.6 (1A3), U4.8 (1A4), U8.2 (RES_OUT)
~RC4_CLKREQ: J7.52 (~CLKREQ), JP12.1
~RC4_RST: J7.50 (~PERST), U4.9 (2Y1)
~SWRC1_CLKREQ: J15.B12 (~CLKREQ), JP14.1
~SWRC1_RST: J15.A11 (~PERST), U4.5 (2Y3)
~SW_RST0: J11.A11 (~PERST), U4.18 (1Y1)
~SW_RST1: J12.A11 (~PERST), U4.16 (1Y2)
~SW_RST2: J13.50 (~PERST), U4.14 (1Y3)
~SW_RST3: J14.50 (~PERST), U4.12 (1Y4)

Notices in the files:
PCBs/openPCIE_openpci2-backplane/processed.kicad_pcb:
CERN-OHL-P
PCBs/openeew-sensor_pcb/processed.kicad_pcb:
licensed under the Apache Software License, Version 2
